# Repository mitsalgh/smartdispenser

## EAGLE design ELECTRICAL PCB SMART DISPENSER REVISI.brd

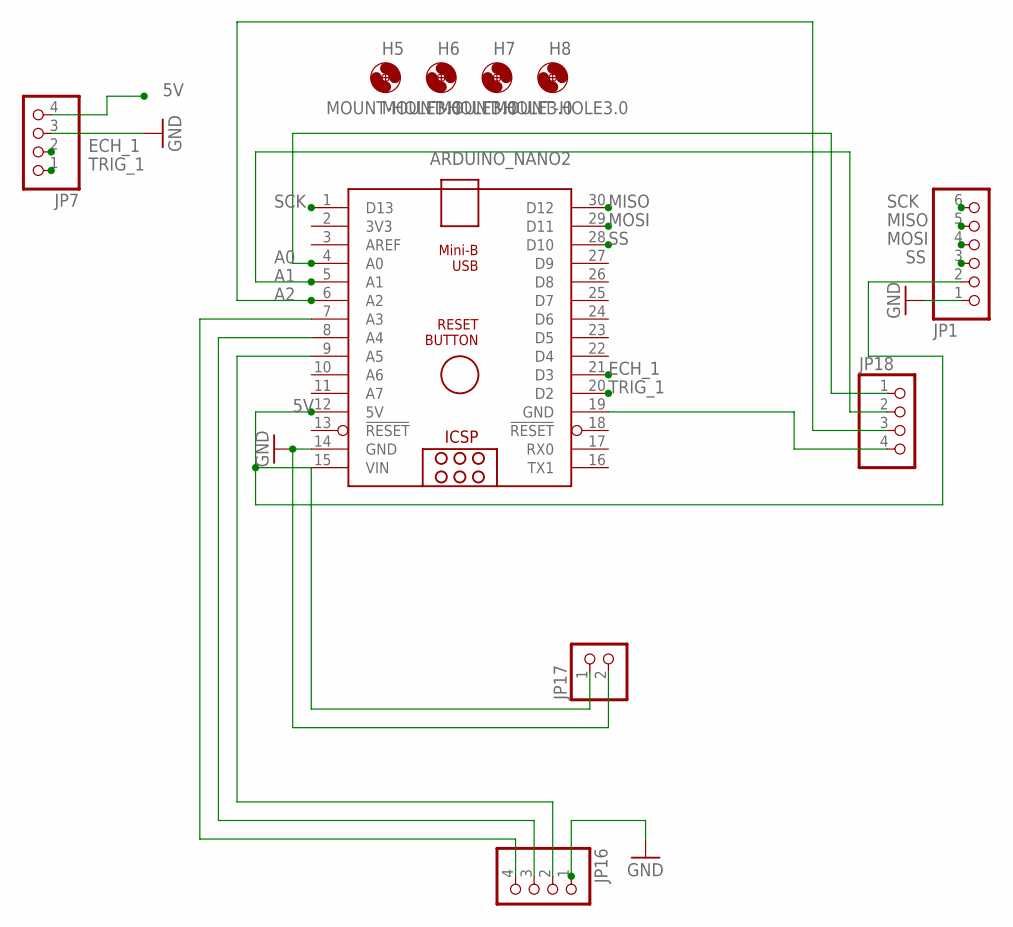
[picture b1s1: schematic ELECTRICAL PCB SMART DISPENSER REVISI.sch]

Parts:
ARDUINO_NANO2: ARDUINO_NANO
H5, H6, H7, H8: MOUNT-HOLE3.0; 3,0
JP1: PINHD-1X6; 1X06
JP7, JP16, JP18: PINHD-1X4; 1X04
JP17: PINHD-1X2; 1X02

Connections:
5V: ARDUINO_NANO2.12 (5V), ARDUINO_NANO2.15 (VIN), JP1.2, JP7.4, JP17.1
A0: ARDUINO_NANO2.4 (A0), JP18.1
A1: ARDUINO_NANO2.5 (A1), JP18.2
A2: ARDUINO_NANO2.6 (A2), JP18.3
A4: ARDUINO_NANO2.9 (A5), JP16.2
A6: ARDUINO_NANO2.7 (A3), JP16.4
ECH_1: ARDUINO_NANO2.21 (D3), JP7.2
GND: ARDUINO_NANO2.14 (GND), JP1.1, JP7.3, JP16.1, JP17.2
MISO: ARDUINO_NANO2.30 (D12), JP1.5
MOSI: ARDUINO_NANO2.29 (D11), JP1.4
unnamed: ARDUINO_NANO2.8 (A4), JP16.3
unnamed: ARDUINO_NANO2.19 (GND), JP18.4
SCK: ARDUINO_NANO2.1 (D13), JP1.6
SS: ARDUINO_NANO2.28 (D10), JP1.3
TRIG_1: ARDUINO_NANO2.20 (D2), JP7.1

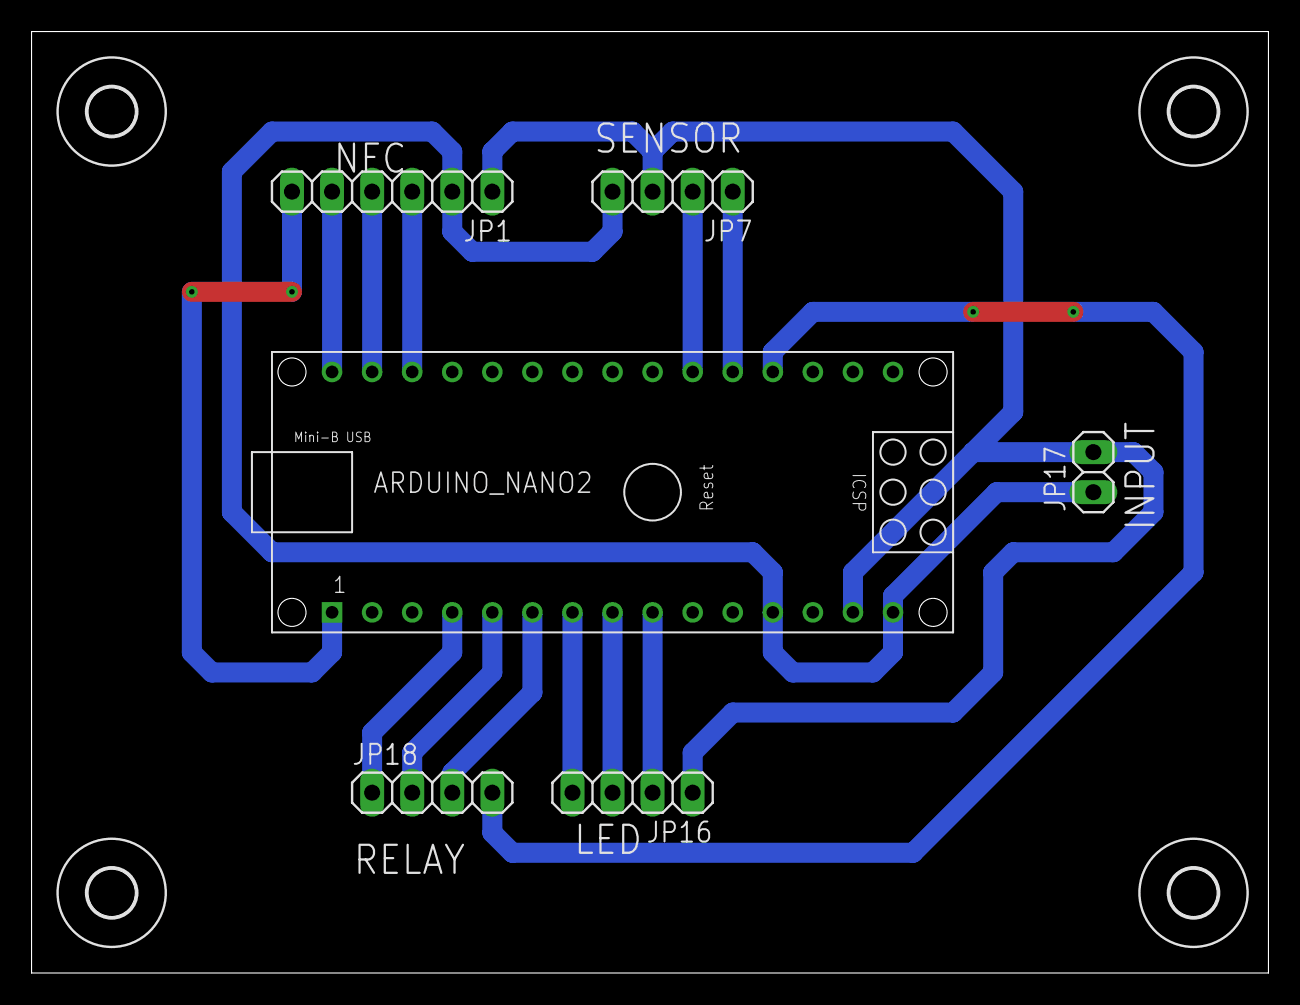
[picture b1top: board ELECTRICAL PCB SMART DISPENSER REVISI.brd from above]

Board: 2 copper layers, 78.4 x 59.7 mm, 10 parts (0 on the bottom side), 15 nets.

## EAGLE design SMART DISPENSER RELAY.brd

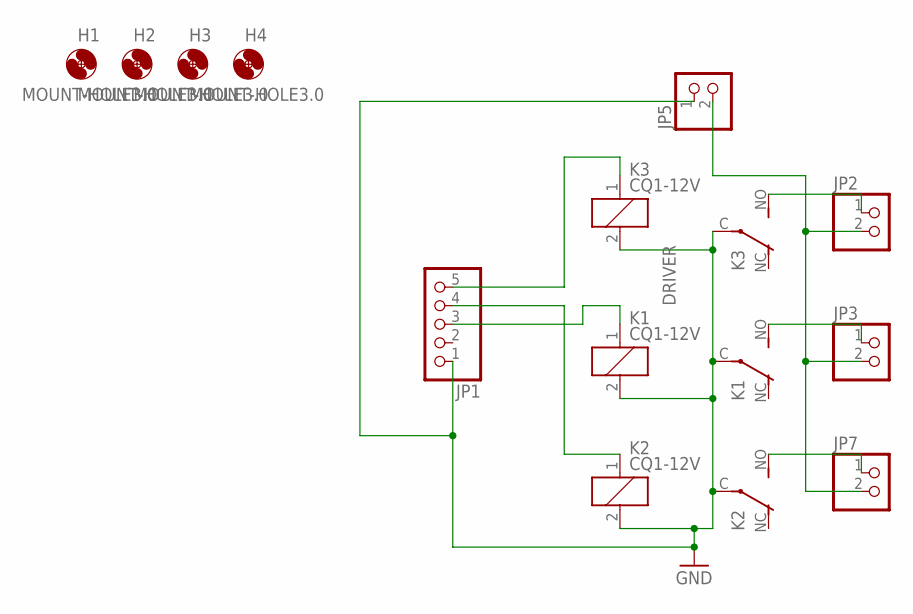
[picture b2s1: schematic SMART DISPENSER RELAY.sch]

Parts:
H1, H2, H3, H4: MOUNT-HOLE3.0; 3,0
JP1: PINHD-1X5; 1X05
JP2, JP3, JP5, JP7: PINHD-1X2; 1X02
K1, K2, K3: CQ1-12V; CQ1

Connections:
GND: JP1.1, JP5.1, K1.2, K1.C, K2.2, K2.C, K3.2, K3.C
unnamed: JP1.5, K3.1
unnamed: JP7.1, K2.NO (S)
unnamed: JP1.3, K1.1
unnamed: JP1.4, K2.1
unnamed: JP2.2, JP3.2, JP5.2, JP7.2
unnamed: JP3.1, K1.NO (S)
unnamed: JP2.1, K3.NO (S)

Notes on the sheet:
DRIVER

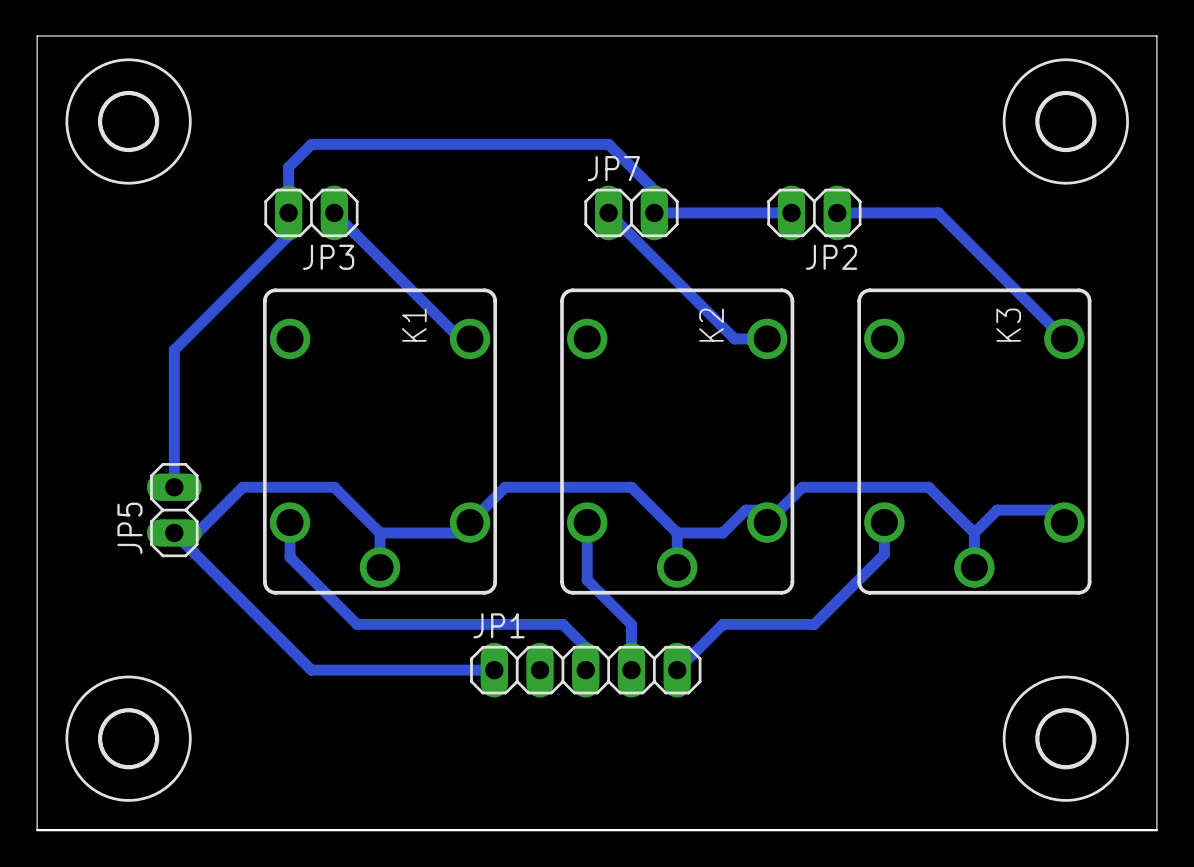
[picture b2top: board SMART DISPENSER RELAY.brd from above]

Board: 2 copper layers, 62.2 x 44.1 mm, 12 parts (0 on the bottom side), 8 nets.
